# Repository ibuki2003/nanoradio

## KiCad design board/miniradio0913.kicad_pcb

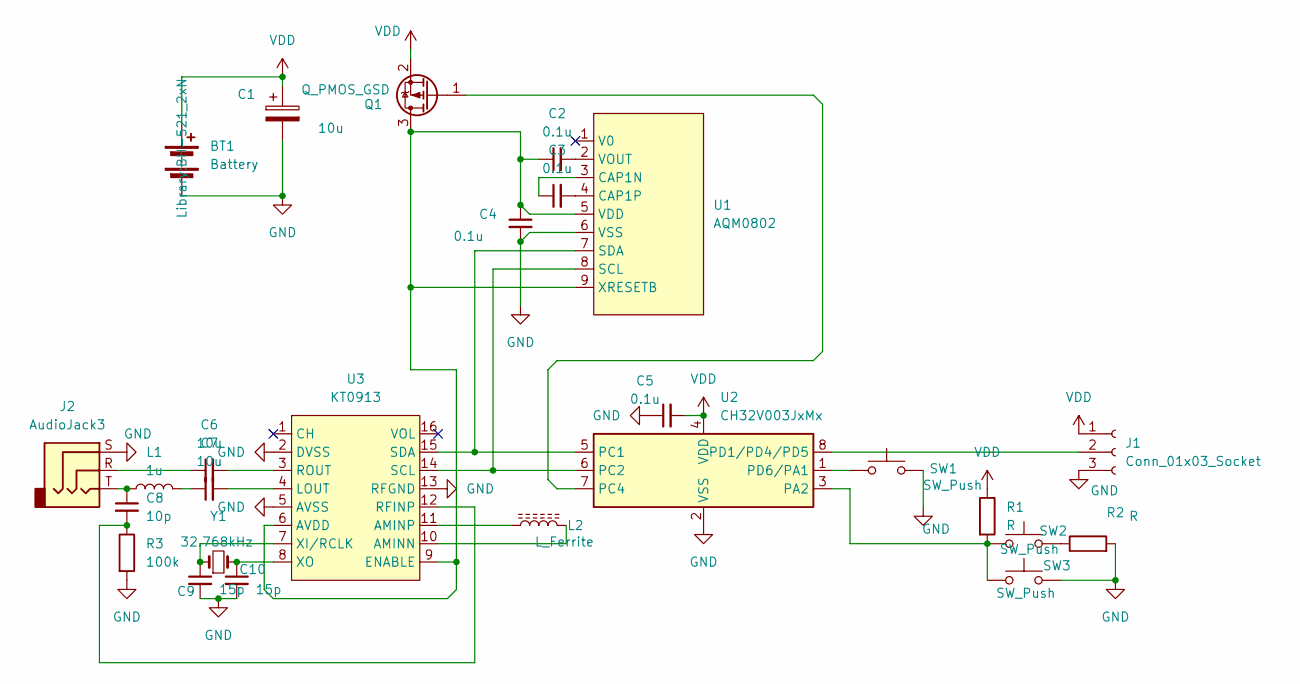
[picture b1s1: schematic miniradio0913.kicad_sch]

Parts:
BT1: Battery; BH-521_2xN
C1, C6, C7: 10u; C_0603_1608Metric
C2, C3, C4, C5: 0.1u; C_0603_1608Metric
C8: 10p; C_0603_1608Metric
C9, C10: 15p; C_0603_1608Metric
J1: Conn_01x03_Socket; DebugPoint_2.54mmx3
J2: AudioJack3; Jack_3.5mm_Switronic_ST-005-G_horizontal
L1: 1u; L_0603_1608Metric
L2: L_Ferrite; L_Axial_L7.0mm_D3.3mm_P10.16mm_Horizontal_Fastron_MICC
Q1: Q_PMOS_GSD; SOT-23
R1, R2: R; R_0603_1608Metric
R3: 100k; R_0603_1608Metric
SW1, SW2, SW3: SW_Push; SW_SPST_PTS810
U1: AQM0802; AQM0802A
U2: CH32V003JxMx; SOP-8_3.9x4.9mm_P1.27mm
U3: KT0913; SSOP-16_3.9x4.9mm_P0.635mm
Y1: 32.768kHz; Crystal_SMD_3215-2Pin_3.2x1.5mm

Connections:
GND: BT1.2 (-), C1.2, C4.2, C5.1, C9.2, C10.2, J1.3, J2.S, R2.2, R3.2, SW1.2, SW3.2, U1.6 (VSS), U2.2 (VSS), U3.2 (DVSS), U3.5 (AVSS), U3.13 (RFGND)
unnamed: C6.1, J2.R
unnamed: C7.1, L1.2
unnamed: C8.1, J2.T, L1.1
unnamed: J1.2, U2.8 (PD1/PD4/PD5)
unnamed: C2.1, C4.1, Q1.3 (D), U1.5 (VDD), U1.9 (XRESETB), U3.6 (AVDD), U3.9 (ENABLE)
unnamed: Q1.1 (G), U2.7 (PC4)
unnamed: R2.1, SW2.2
unnamed: C3.1, U1.3 (CAP1N)
unnamed: C3.2, U1.4 (CAP1P)
unnamed: U1.8 (SCL), U2.6 (PC2), U3.14 (SCL)
unnamed: U1.7 (SDA), U2.5 (PC1), U3.15 (SDA)
unnamed: C2.2, U1.2 (VOUT)
unnamed: R1.2, SW2.1, SW3.1, U2.3 (PA2)
unnamed: SW1.1, U2.1 (PD6/PA1)
unnamed: L2.1, U3.10 (AMINN)
unnamed: L2.2, U3.11 (AMINP)
unnamed: C7.2, U3.4 (LOUT)
unnamed: C8.2, R3.1, U3.12 (RFINP)
unnamed: C6.2, U3.3 (ROUT)
unnamed: C9.1, U3.7 (XI/RCLK), Y1.1
unnamed: C10.1, U3.8 (XO), Y1.2
VDD: BT1.1 (+), C1.1, C5.2, J1.1, Q1.2 (S), R1.1, U2.4 (VDD)

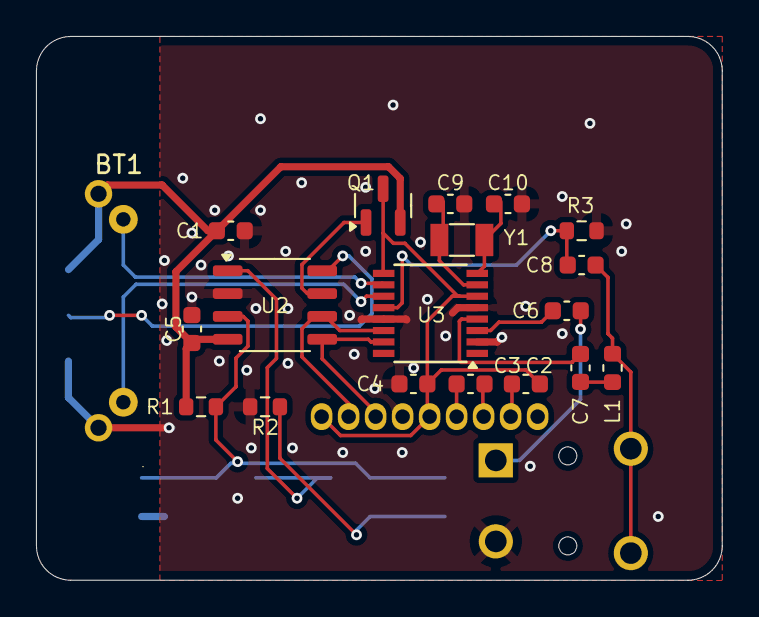
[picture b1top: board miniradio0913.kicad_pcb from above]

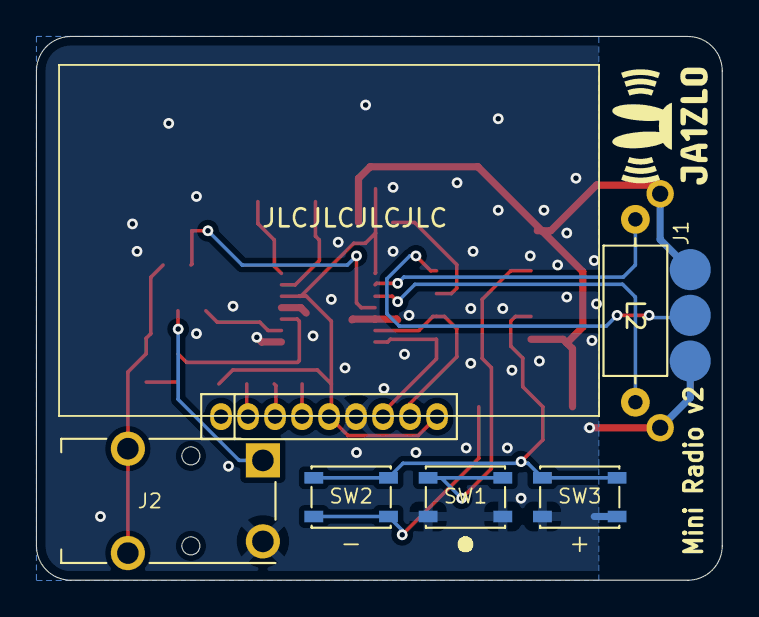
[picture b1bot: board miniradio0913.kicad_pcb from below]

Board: 2 copper layers, 38.1 x 30.2 mm, 26 parts (7 on the bottom side), 23 nets.

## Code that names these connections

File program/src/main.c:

#include "ch32v003fun.h"
#include <sys/types.h>
#include <stdint.h>

#include <buttons.h>
#include <adc.h>
#include <pwr.h>
#include <i2c.h>
#include <lcd.h>
#include <kt0913.h>
#include <freqs.h>
#include <utils.h>
#include <lcd_kana.h>

// will be called on startup and after wake-up
void setup() {
  SystemInit();
  Delay_Ms(100);

  RCC->APB1PCENR |= RCC_APB1Periph_I2C1;
  RCC->APB2PCENR |= (0
    | RCC_APB2Periph_AFIO
    | RCC_APB2Periph_GPIOA
    | RCC_APB2Periph_GPIOC
    // | RCC_APB2Periph_GPIOD
    | RCC_APB2Periph_ADC1
    | RCC_AFIOEN
  );

  funPinMode(PA1, GPIO_Speed_In | GPIO_CNF_IN_PUPD);   // btn2: pull-up
  funPinMode(PA2, GPIO_Speed_In | GPIO_CNF_IN_ANALOG); // btn1, 3: analog
  funPinMode(PC4, GPIO_Speed_2MHz | GPIO_CNF_OUT_PP);  // power FET

  // PC1: SDA, PC2: SCL
  funPinMode(PC1, GPIO_Speed_10MHz | GPIO_CNF_OUT_OD_AF);
  funPinMode(PC2, GPIO_Speed_10MHz | GPIO_CNF_OUT_OD_AF);

  funDigitalWrite(PC4, 0); // set down to turn on FET
  funDigitalWrite(PA1, 1); // pull-up

  Delay_Ms(100);

  // ADC Setup
  adc_init();

  i2c_setup();
}

typedef enum {
  MODE_NORMAL = 0,
  MODE_FREQ,
  MODE_CONFIG,
  MODE_SLEEP,
} Mode;

// global state
bool am = false;
uint16_t am_freq = 594;
uint16_t fm_freq = 800;
uint8_t vol = 16;
uint8_t area = 2; // kanto

void draw_l1(bool seeking) {
  uint8_t sbuf[9];
  sbuf[0] = 0x40;

  sbuf[2] = 'M';
  sbuf[3] = ' ';
  sbuf[4] = ' ';

  if (am) {
    // 12345678
    // AM  594k
    sbuf[1] = 'A';

    my_itoa(am_freq, &sbuf[7], 4);

    sbuf[8] = 'k';
  } else {
    // 12345678
    // FM 84.7M
    sbuf[1] = 'F';

    my_itoa(fm_freq, &sbuf[6], 4);

    sbuf[7] = sbuf[6];
    sbuf[6] = '.';
    sbuf[8] = 'M';
  }

  if (seeking) {
    if (sbuf[3] == ' ') sbuf[3] = 0xfb;
    sbuf[8] = 0xfc;
  }

  LCD_send_command(0x80);
  i2c_send(I2C_LCD_ADDR, sbuf, 9);
}

void draw_station_name() {
  uint8_t sbuf[9];
  sbuf[0] = 0x40;

  char const* const name = find_station(am ? am_freq : fm_freq, am, area);
  if (name) {
    my_strcpy(&sbuf[1], (const uint8_t*)name);
  } else {
    sbuf[1] = '-';
    for (uint i = 2; i < 9; ++i) sbuf[i] = ' ';
  }

  // on line 2
  LCD_send_command(0x80 | 0x40);
  i2c_send(I2C_LCD_ADDR, sbuf, 9);
}

void add_freq(int8_t d) {
  if (am) {
    am_freq += 9 * d;
    if (am_freq < AM_FREQ_MIN) am_freq = AM_FREQ_MAX;
    if (am_freq > AM_FREQ_MAX) am_freq = AM_FREQ_MIN;
    KT0913_set_freq_am(am_freq);
  } else {
    fm_freq += 1 * d;
    if (fm_freq < FM_FREQ_MIN) fm_freq = FM_FREQ_MAX;
    if (fm_freq > FM_FREQ_MAX) fm_freq = FM_FREQ_MIN;
    KT0913_set_freq_fm(fm_freq);
  }
}

#define LOOP_INTERVAL 10

#define VOLUME_SHOW_TIMEOUT 50
Mode run_normal() {
  // initialize
  draw_l1(false);
  draw_station_name();

  uint16_t volume_timeout = 0;

  while(1) {

    uint8_t k = get_buttons();
    bool timedout = volume_timeout == 1;
    if (volume_timeout) volume_timeout--;

    if (k || timedout) {

      if (button_hold[0] % 8 == 1) {
        if (vol > 0) --vol;
        KT0913_set_vol(vol);
        volume_timeout = VOLUME_SHOW_TIMEOUT;
      }
      if (button_hold[2] % 8 == 1) {
        if (vol < 31) ++vol;
        KT0913_set_vol(vol);
        volume_timeout = VOLUME_SHOW_TIMEOUT;
      }

      if (button_release[1]) {
        return MODE_FREQ;
      }

      if (button_hold[1] >= 200) {
        mark_buttons_handled(0b010);
        // go to sleep
        // turn off FET
        funDigitalWrite(PC4, 1);
        // wait for release
        while (funDigitalRead(PA1) == 0) {}
        return MODE_SLEEP;
      }

      // draw

      // freq won't change
      // draw_l1(false);

      if (volume_timeout) {
        uint8_t sbuf[9];
        sbuf[0] = 0x40;
        for (uint i = 1; i < 9; ++i) sbuf[i] = ' ';

        uint16_t v = vol;
        if (v == 1) v = 0;
        uint8_t bar_len = v / 5;
        if (bar_len)
          for (uint i = 0; i < bar_len; ++i)
            sbuf[i+1] = CHAR_BLACK;
        sbuf[bar_len+1] = CHAR_BAR_PART;

        LCD_make_bar_font(v % 5);

        v = vol == 31 ? 99 : vol * 100 / 31;
        my_itoa(v, &sbuf[8], 2);

        LCD_send_command(0x80 | 0x40);
        i2c_send(I2C_LCD_ADDR, sbuf, 9);
      } else {
        draw_station_name();
      }
    }

    Delay_Ms(LOOP_INTERVAL);
  }
}

#define FREQ_TIMEOUT 200
Mode run_freq() {
  uint16_t timeout = FREQ_TIMEOUT;
  // initialize
  draw_l1(true);
  draw_station_name();

  while(1) {

    uint8_t k = get_buttons();

    if (k) {
      timeout = FREQ_TIMEOUT;
      if (button_hold[0] == 1 || button_hold[0] >= 50) {
        add_freq(-1);
      }
      if (button_hold[2] == 1 || button_hold[2] >= 50) {
        add_freq(1);
      }

      if (button_release[1]) {
        am = !am;
        KT0913_set_amfm(am);
        if (am) {
          KT0913_set_freq_am(am_freq);
        } else {
          KT0913_set_freq_fm(fm_freq);
        }
      }

      if (button_hold[1] >= 200) {
        mark_buttons_handled(0b010);
        // go to config
        return MODE_CONFIG;
      }

      // draw
      draw_l1(true);
      draw_station_name();
    }

    if (--timeout == 0) {
      return MODE_NORMAL;
    }

    Delay_Ms(LOOP_INTERVAL);
  }
}

#define CONFIG_TIMEOUT 1000
Mode run_config() {
  uint16_t timeout = CONFIG_TIMEOUT;
  // initialize

  uint8_t sbuf[9];
  sbuf[0] = 0x40;

  LCD_send_command(0x80);
  i2c_send(I2C_LCD_ADDR, (const uint8_t*)("\x40" ｴ ﾘ ｱ ｾ ｯ ﾃ ｲ " "), 9);


  my_strcpy(&sbuf[1], (const uint8_t*)AREAS[area]);
  LCD_send_command(0x80 | 0x40);
  i2c_send(I2C_LCD_ADDR, sbuf, 9);

  while(1) {

    uint8_t k = get_buttons();

    if (k) {
      timeout = FREQ_TIMEOUT;
      if (button_hold[0] % 16 == 1) {
        area = (area + AREA_COUNT - 1) % AREA_COUNT;
      }
      if (button_hold[2] == 1 || button_hold[2] >= 50) {
        area = (area + 1) % AREA_COUNT;
      }

      if (button_release[1] || button_hold[1] >= 200) {
        mark_buttons_handled(0b010);
        return MODE_NORMAL;
      }

      // draw
      my_strcpy(&sbuf[1], (const uint8_t*)AREAS[area]);
      LCD_send_command(0x80 | 0x40);
      i2c_send(I2C_LCD_ADDR, sbuf, 9);
    }

    if (--timeout == 0) {
      return MODE_NORMAL;
    }

    Delay_Ms(LOOP_INTERVAL);
  }
}

void inner_main() {
  // here cpu is after power-up or wake-up
  setup();

  // Initialize LCD
  LCD_init();

  LCD_send_command(0x80);
  i2c_send(I2C_LCD_ADDR, (const uint8_t*)("\x40HELLO"), 6);

  // reset button state
  get_buttons();
  mark_buttons_handled(0b111);

  Delay_Ms(100);

  // Initialize IC
  KT0913_init();
  KT0913_set_vol(vol);


  KT0913_set_amfm(am);
  KT0913_set_freq_fm(fm_freq);
  KT0913_set_freq_am(am_freq);

  find_station_refresh(am ? am_freq : fm_freq, am, area);

  Mode mode = MODE_NORMAL;
  while (true) {
    switch (mode) {
      case MODE_NORMAL:
        mode = run_normal();
        break;
      case MODE_FREQ:
        mode = run_freq();
        break;
      case MODE_CONFIG:
        mode = run_config();
        break;
      case MODE_SLEEP:
        Delay_Ms(100);
        sleep();
        return; // Run setup again
        break;
    }
    Delay_Ms(LOOP_INTERVAL);
  }

}


int main() {
  while (1) {
    inner_main();
  }
}

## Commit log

2024-07-10 feat: setup ch32v003fun
2024-07-20 add board
2024-07-20 fix(board): crystal
2024-07-20 feat: add i2c lib
2024-08-11 build: add funconfig.h as make deps
2024-08-11 feat: use HSI
2024-08-11 feat: add sleep util
2024-08-11 feat: add lcd utils
2024-08-11 board: update
2024-08-20 feat: update i2c lib
2024-08-20 feat: add kt0913 lib
2024-08-20 feat: it works
2024-08-20 feat: update board (release v1)
2024-08-20 feat: add freqs data
2024-08-20 feat: add progressbar characters to CGRAM
2024-08-20 feat: sleep mode
2024-08-22 feat: efficient station search
2024-08-22 feat: show station name
2024-08-22 fix: wait for i2c ready before start to use
2024-08-22 feat: update i2c libs
2024-08-22 feat: update buttons logic
2024-08-22 feat: add some custom char glyphs
2024-08-22 feat: control UI
2024-08-22 fix: radio freq range
2024-08-22 feat: edit freqs
2024-08-23 feat: disable softmute
2024-08-23 feat: add delay after wakeup
2024-08-23 feat: increase lcd contrast
2024-08-23 feat: update freqs
2024-08-23 fix: decrease i2c speed
2024-08-23 fix: set freq on mode change
2024-08-23 fix: update wakeup logic
2024-09-10 feat(board): update layout
2024-10-15 board: renumber parts
2024-10-15 board: fix wiring
2024-10-18 update board
2024-11-08 fix: set am freq after wakeup
